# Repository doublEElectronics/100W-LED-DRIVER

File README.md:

100W-LED-DRIVER
===============

A LM3409HV based driver to run 2.5A-3.5A leds with various config options

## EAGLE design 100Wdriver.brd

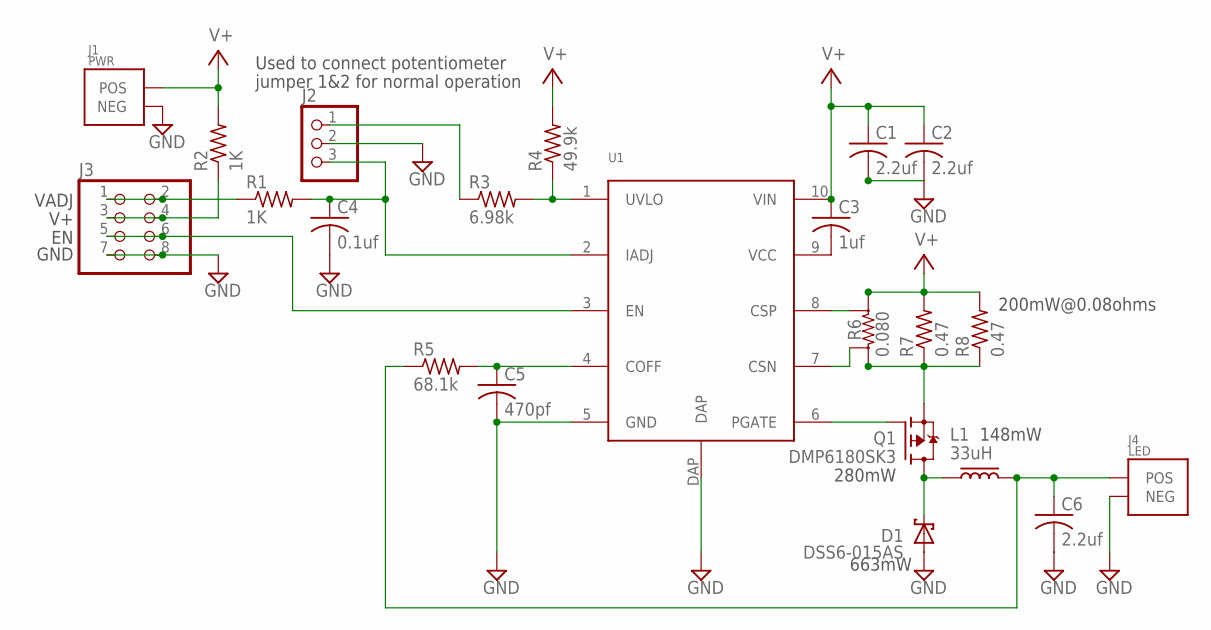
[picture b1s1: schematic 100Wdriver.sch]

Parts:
C1, C2, C6: 2.2uf; C1210
C3: 1uf; C0805
C4: 0.1uf; C0805
C5: 470pf; C0805
D1: DSS6-015AS; D-PAK_TO252AA
J1: PWR; 3.5MMLEFT
J2: PINHD-1X3; 1X03
J3: PINHD-2X4; 2X04
J4: LED; 3.5MM
L1: 33uH; SDR2207
Q1: DMP6180SK3; TO252
R1, R2: 1K; R0805
R3: 6.98k; R0805
R4: 49.9k; R0805
R5: 68.1k; R0805
R6: 0.080; 2512SENSE
R7, R8: 0.47; R1206
U1: LM3409HV; 10VSSOP

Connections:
EN: J3.5, J3.6, U1.3 (EN)
GND: C1.2, C2.2, C4.2, C5.2, C6.2, D1.1 (A), D1.3 (A), J1.GND (NEG), J2.2, J3.7, J3.8, J4.NEGATIVE (NEG), U1.5 (GND), U1.DAP
IADJ: C4.1, J2.3, R1.2, U1.2 (IADJ)
unnamed: Q1.2 (S), R6.P$3, R6.P$4, R7.1, R8.1
unnamed: C5.1, R5.2, U1.4 (COFF)
unnamed: R3.2, R4.1, U1.1 (UVLO)
unnamed: D1.4 (C), L1.P$1, Q1.3 (D)
unnamed: C3.2, U1.9 (VCC)
unnamed: Q1.1 (G), U1.6 (PGATE)
unnamed: C6.1, J4.POSITIVE (POS), L1.P$2, R5.1
unnamed: J3.1, J3.2, R1.1
unnamed: J2.1, R3.1
unnamed: J3.3, J3.4, R2.1
unnamed: R6.SNS1, U1.8 (CSP)
unnamed: R6.SNS2, U1.7 (CSN)
V+: C1.1, C2.1, C3.1, J1.V+ (POS), R2.2, R4.2, R6.P$1, R6.P$2, R7.2, R8.2, U1.10 (VIN)

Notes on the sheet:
GND
VADJ
Used to connect potentiometer
jumper 1&2 for normal operation
280mW
663mW
148mW
200mW@0.08ohms

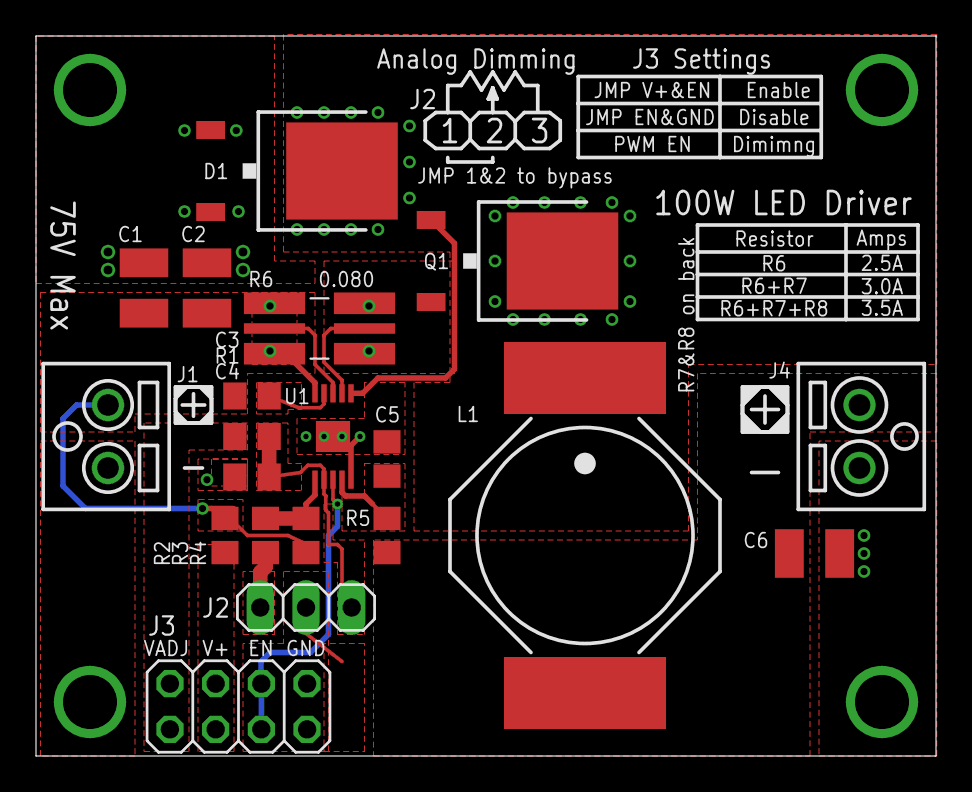
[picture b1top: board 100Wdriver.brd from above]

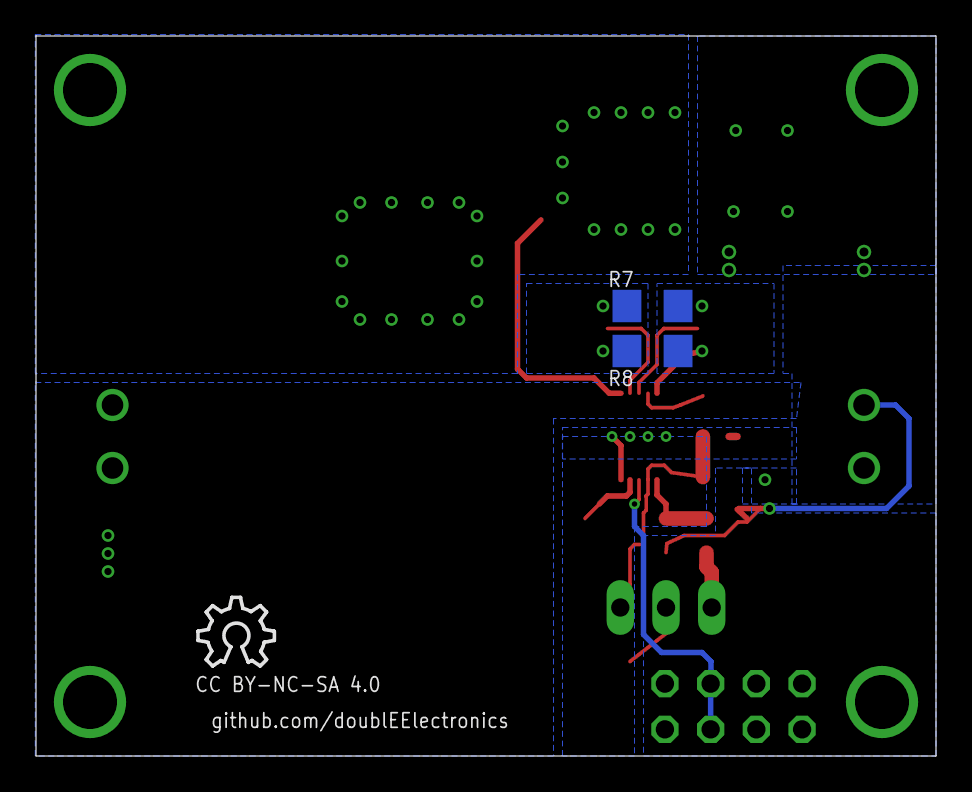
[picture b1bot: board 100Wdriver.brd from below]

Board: 2 copper layers, 50.0 x 40.0 mm, 23 parts (3 on the bottom side), 16 nets.

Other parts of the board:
U$1: OSHW_8X150_NOTEXT

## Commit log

2014-07-20 added Schematic/PCB/library/BOM and CC license

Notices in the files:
100Wdriver.brd:
CC BY-NC-SA 4.0
